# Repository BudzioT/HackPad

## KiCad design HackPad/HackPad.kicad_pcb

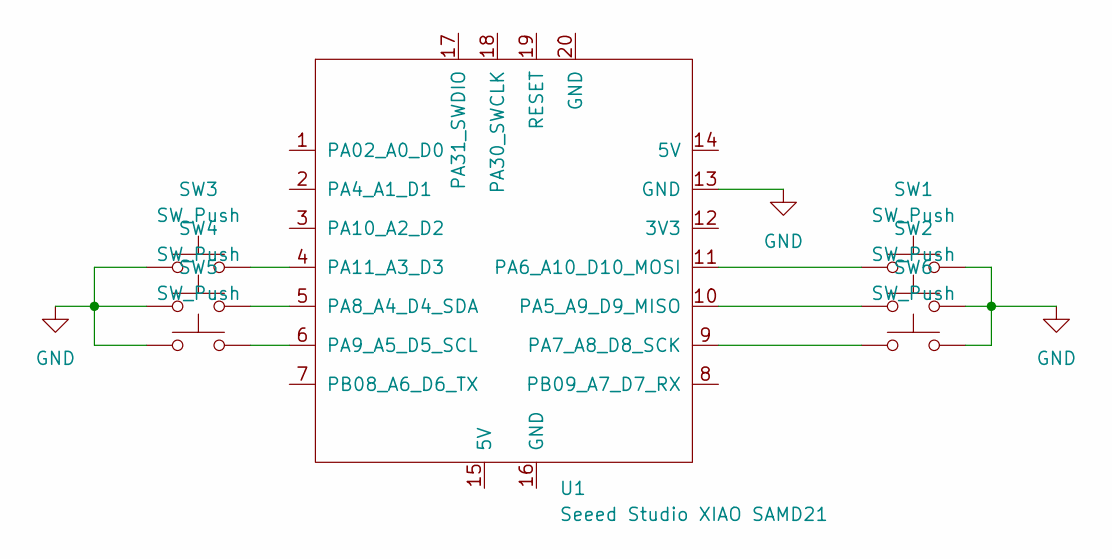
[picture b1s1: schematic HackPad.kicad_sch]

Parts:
SW1, SW2, SW3, SW4, SW5, SW6: SW_Push; SW_Cherry_MX_1.00u_PCB
U1: Seeed Studio XIAO SAMD21; XIAO-Generic-Thruhole-14P-2.54-21X17.8MM

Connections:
GND: SW1.2, SW2.2, SW3.1, SW4.1, SW5.1, SW6.2, U1.13 (GND)
unnamed: SW2.1, U1.10 (PA5_A9_D9_MISO)
unnamed: SW1.1, U1.11 (PA6_A10_D10_MOSI)
unnamed: SW6.1, U1.9 (PA7_A8_D8_SCK)
unnamed: SW4.2, U1.5 (PA8_A4_D4_SDA)
unnamed: SW5.2, U1.6 (PA9_A5_D5_SCL)
unnamed: SW3.2, U1.4 (PA11_A3_D3)

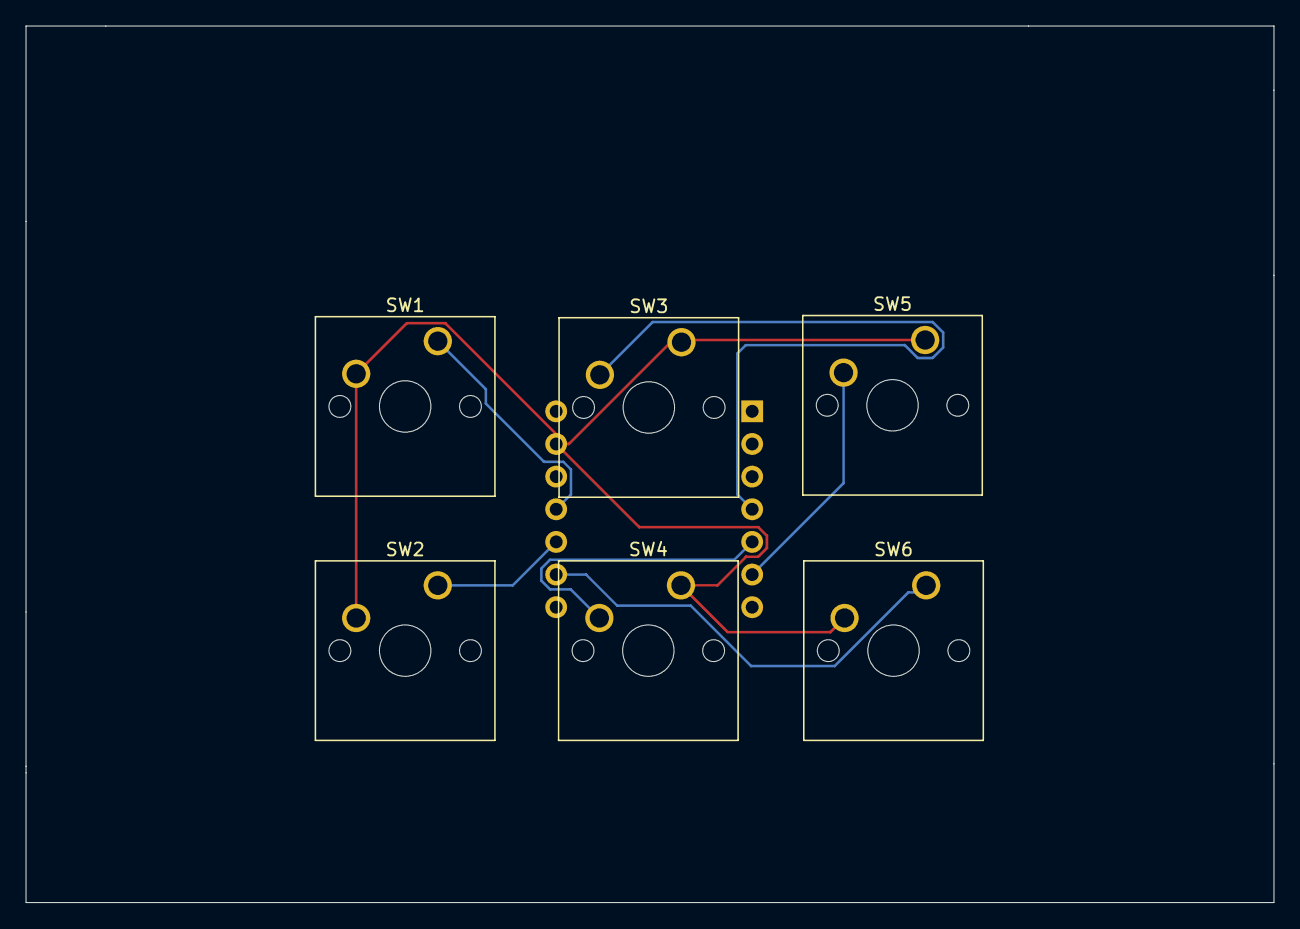
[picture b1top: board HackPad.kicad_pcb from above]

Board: 2 copper layers, 97.1 x 68.2 mm, 7 parts (1 on the bottom side), 7 nets.

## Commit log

2024-09-25 Initialized libs
2024-09-25 Added basic schematatisc, starter switches
2024-09-25 Added switches
2024-10-03 Reset
2024-10-03 Actually started building, finished wiring???
